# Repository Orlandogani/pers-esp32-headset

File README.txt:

This project is for custom headset Electronics PCB Routing. The name is coming from the acronym of my own name.

ORGA: Omni Radiant Gaming Apparatus
Vibe & Product Fit: Flagship RGB peripherals—think high-end wireless mice and master-class headsets designed for professional esports athletes who demand absolute dominance.

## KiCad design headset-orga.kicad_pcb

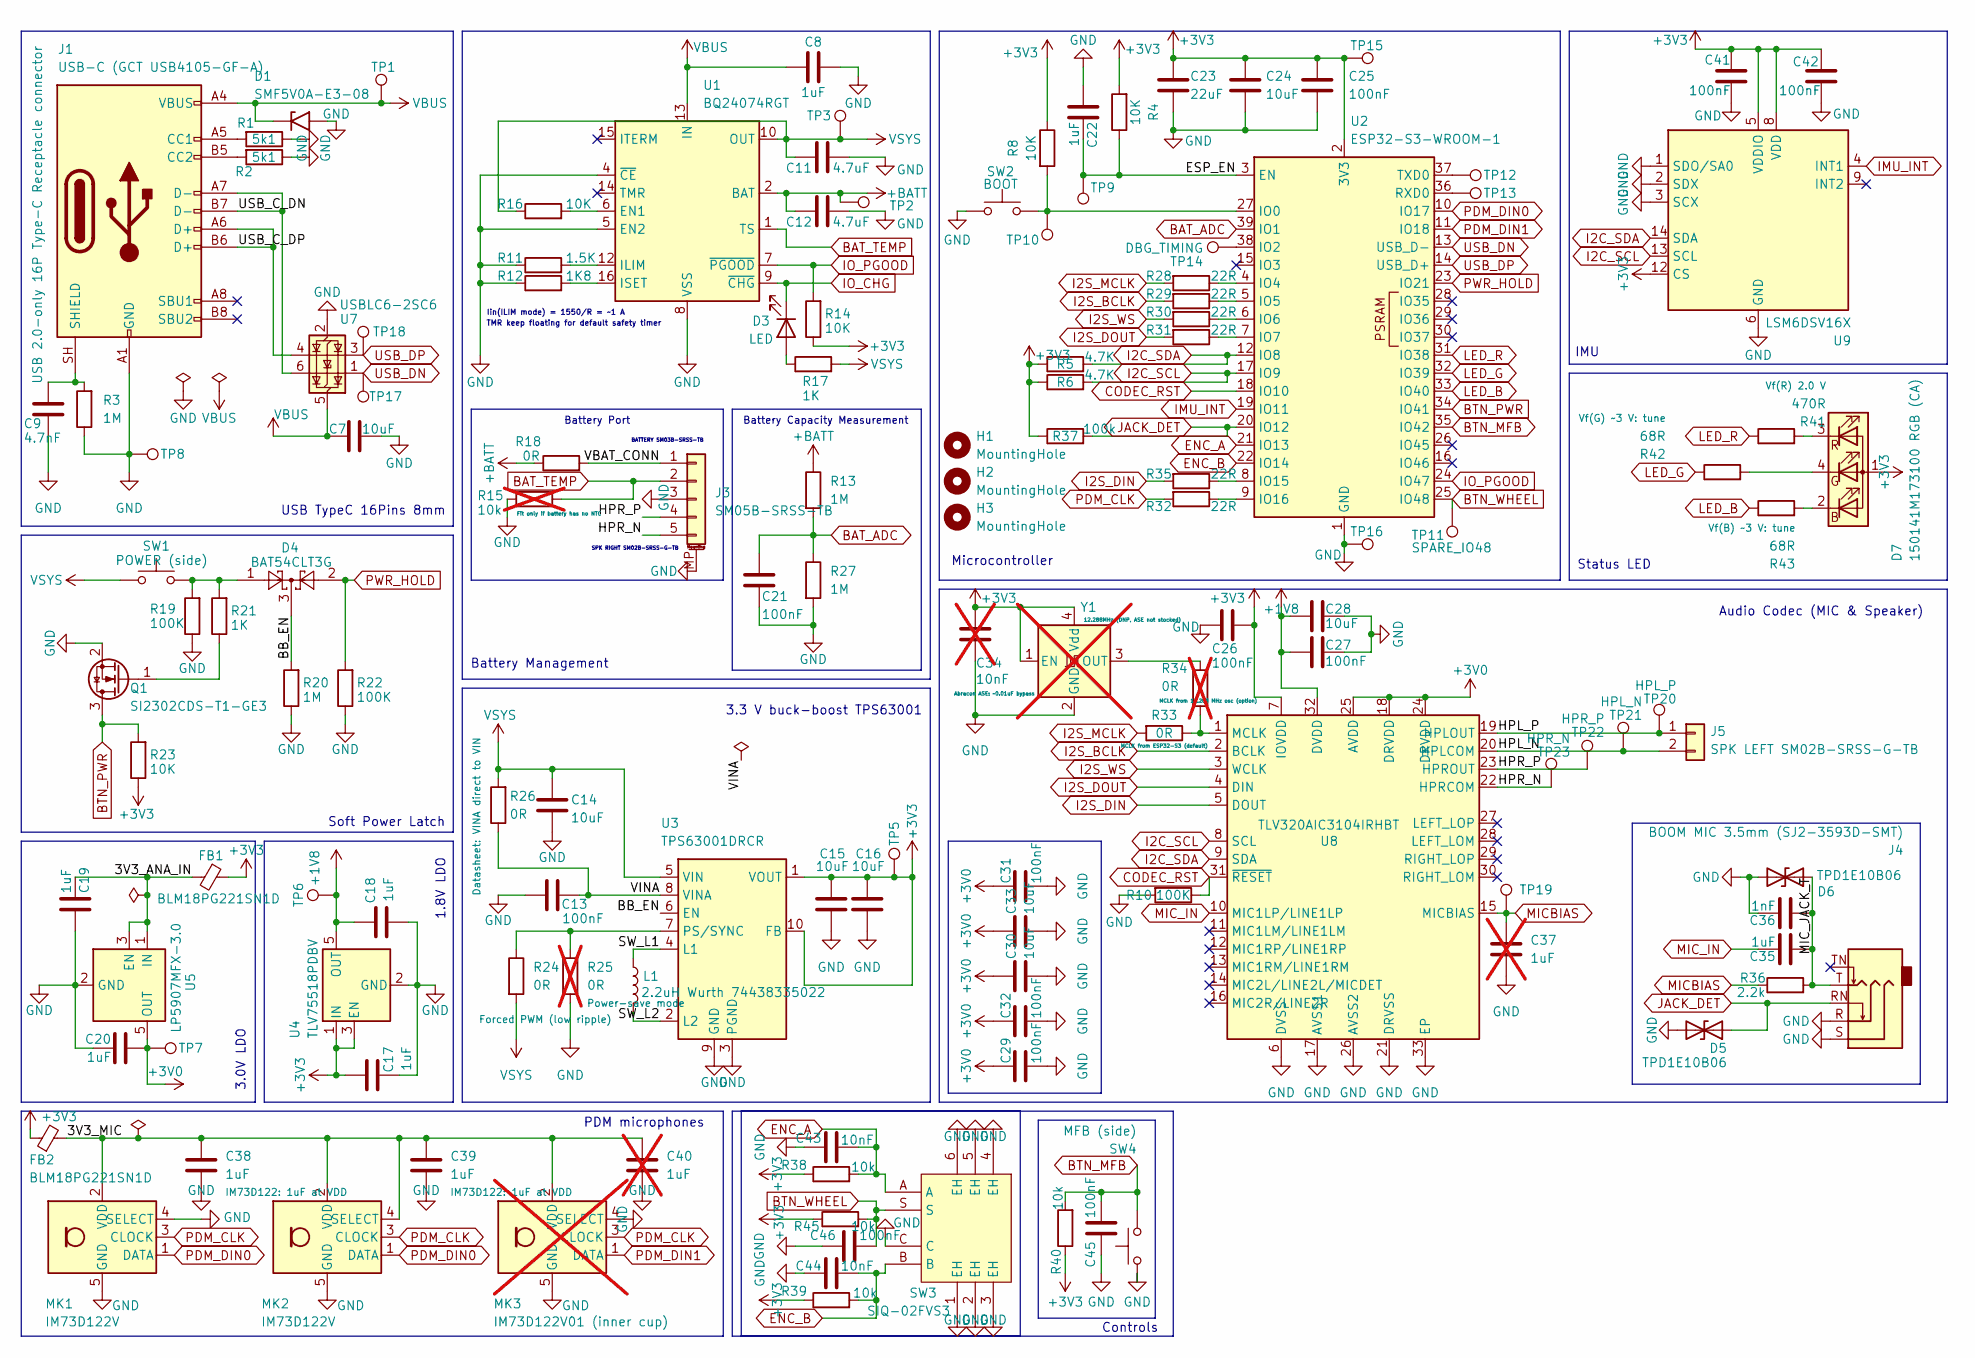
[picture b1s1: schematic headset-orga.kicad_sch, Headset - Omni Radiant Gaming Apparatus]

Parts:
C7: 10uF; C_0805_2012Metric
C8, C17, C18, C19, C20: 1uF; C_0603_1608Metric
C9: 4.7nF; C_0402_1005Metric
C11, C12: 4.7uF; C_0603_1608Metric
C13, C21, C25, C26, C27, C29, C31, C32, C41, C42, C45, C46: 100nF; C_0402_1005Metric
C14, C15, C16, C24: 10uF; C_0603_1608Metric
C22, C35, C38, C39: 1uF; C_0402_1005Metric
C23: 22uF; C_0805_2012Metric
C28, C30, C33: 10uF; C_0402_1005Metric
C34: 10nF; C_0402_1005Metric; not fitted
C36: 1nF; C_0402_1005Metric
C37, C40: 1uF; C_0402_1005Metric; not fitted
C43, C44: 10nF; C_0402_1005Metric
D1: SMF5V0A-E3-08; D_SMF
D3: LED; LED_0603_1608Metric
D4: BAT54CLT3G; SOT-23
D5, D6: TPD1E10B06; D_0402_1005Metric
D7: 150141M173100 RGB (CA); LED_RGB_Wuerth-PLCC4_3.2x2.8mm_150141M173100
FB1, FB2: BLM18PG221SN1D; L_0603_1608Metric
H1, H2, H3: MountingHole; MountingHole_2.4mm_M2
J1: USB-C (GCT USB4105-GF-A); USB_C_Receptacle_GCT_USB4105-xx-A_16P_TopMnt_Horizontal
J3: SM05B-SRSS-TB; JST_SH_SM05B-SRSS-TB_1x05-1MP_P1.00mm_Horizontal
J4: BOOM MIC 3.5mm (SJ2-3593D-SMT); Jack_3.5mm_CUI_SJ2-3593D-SMT_Horizontal
J5: SPK LEFT SM02B-SRSS-G-TB; JST_SH_SM02B-SRSS-TB_1x02-1MP_P1.00mm_Horizontal
L1: 2.2uH Wurth 74438335022; L_Wuerth_MAPI-3015
MK1, MK2: IM73D122V; Infineon_PG-LLGA-5-3_IM73D122
MK3: IM73D122V01 (inner cup); Infineon_PG-LLGA-5-3_IM73D122; not fitted
Q1: SI2302CDS-T1-GE3; SOT-23
R1, R2: 5k1; R_0603_1608Metric
R3, R20: 1M; R_0603_1608Metric
R4, R8, R14, R16, R23: 10K; R_0603_1608Metric
R5, R6: 4.7K; R_0603_1608Metric
R10, R19, R22: 100K; R_0603_1608Metric
R11: 1.5K; R_0603_1608Metric
R12: 1K8; R_0603_1608Metric
R13, R27: 1M; R_0402_1005Metric
R15: 10k; R_0402_1005Metric; not fitted
R17, R21: 1K; R_0603_1608Metric
R18, R33: 0R; R_0603_1608Metric
R24, R26: 0R; R_0402_1005Metric
R25, R34: 0R; R_0402_1005Metric; not fitted
R28, R29, R30, R31, R32, R35: 22R; R_0603_1608Metric
R36: 2.2k; R_0603_1608Metric
R37: 100k; R_0603_1608Metric
R38, R39, R40, R45: 10k; R_0402_1005Metric
R41: 470R; R_0402_1005Metric
R42, R43: 68R; R_0402_1005Metric
SW1: POWER (side); SW_SPST_EVQP7A
SW2: BOOT; SW_SPST_EVQP7A
SW3: SIQ-02FVS3; SW-SMD_SIQ-02FVS3_1; MPN SIQ-02FVS3; LCSC C2925423
SW4: MFB (side); SW_SPST_EVQP7A
TP1, TP2, TP3, TP5, TP6, TP7, TP8, TP9, TP10, TP15, TP16, TP17, TP18, TP19: TestPoint; TestPoint_Pad_D1.0mm
TP11: SPARE_IO48; TestPoint_Pad_D1.0mm
TP12: TX0; TestPoint_Pad_D1.0mm
TP13: RX0; TestPoint_Pad_D1.0mm
TP14: DBG_TIMING; TestPoint_Pad_D1.0mm
TP20: HPL_P; TestPoint_Pad_D1.0mm
TP21: HPL_N; TestPoint_Pad_D1.0mm
TP22: HPR_P; TestPoint_Pad_D1.0mm
TP23: HPR_N; TestPoint_Pad_D1.0mm
U1: BQ24074RGT; VQFN-16-1EP_3x3mm_P0.5mm_EP1.6x1.6mm_ThermalVias
U2: ESP32-S3-WROOM-1
U3: TPS63001DRCR; Texas_DRC0010J_ThermalVias
U4: TLV75518PDBV; SOT-23-5
U5: LP5907MFX-3.0; SOT-23-5
U7: USBLC6-2SC6; SOT-23-6
U8: TLV320AIC3104IRHBT; Texas_RHB0032E_VQFN-32-1EP_5x5mm_P0.5mm_EP3.45x3.45mm_Therm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
U9: LSM6DSV16X; LGA-14_3x2.5mm_P0.5mm_LayoutBorder3x4y
Y1: 12.288MHz (DNP, ASE not stocked); Oscillator_SMD_Abracon_ASE-4Pin_3.2x2.5mm; not fitted

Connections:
+1V8: C18.2, C27.1, C28.1, TP6.1 (1_1), U4.5 (OUT), U8.32 (DVDD)
+3V0: C20.2, C29.1, C30.1, C31.1, C32.1, C33.1, TP7.1 (1_1), U5.5 (OUT), U8.18 (DRVDD), U8.24 (DRVDD), U8.25 (AVDD)
+3V3: C15.2, C16.2, C17.2, C23.1, C24.1, C25.1, C26.2, C34.1, C41.1, C42.1, D7.1 (A), FB1.1, FB2.1, R4.2, R5.1, R6.1, R8.1, R14.1, R23.1, R37.1, R38.1, R39.1, R40.1, R45.1, TP5.1 (1_1), TP15.1 (1_1), U2.2 (3V3), U3.1 (VOUT), U3.10 (FB), U4.1 (IN), U4.3 (EN), U8.7 (IOVDD), U9.5 (VDDIO), U9.8 (VDD), U9.12 (CS), Y1.1 (EN), Y1.4 (Vdd)
+BATT: C12.1, R13.1, R18.1, TP2.1 (1_1), U1.2 (BAT), U1.3 (BAT)
/3V3_ANA_IN: C19.1, FB1.2, U5.1 (IN), U5.3 (EN)
/3V3_MIC: C38.1, C39.1, C40.1, FB2.2, MK1.2 (VDD), MK2.2 (VDD), MK2.4 (SELECT), MK3.2 (VDD)
/BB_EN: D4.3, R20.2, U3.6 (EN)
/ESP_EN: C22.2, R4.1, TP9.1 (1_1), U2.3 (EN)
/HPL_N: J5.2, TP21.1 (1_1), U8.20 (HPLCOM)
/HPL_P: J5.1, TP20.1 (1_1), U8.19 (HPLOUT)
/HPR_N: J3.5, TP23.1 (1_1), U8.22 (HPRCOM)
/HPR_P: J3.4, TP22.1 (1_1), U8.23 (HPROUT)
/MIC_JACK_T: C35.2, C36.2, D6.1 (A1), J4.T, R36.2
/SW_L1: L1.1, U3.4 (L1)
/SW_L2: L1.2, U3.2 (L2)
/USB_C_DN: J1.A7 (D-), J1.B7 (D-), U7.6 (I/O1)
/USB_C_DP: J1.A6 (D+), J1.B6 (D+), U7.4 (I/O2)
/VBAT_CONN: J3.1, R18.2
/VINA: C13.2, R26.1, U3.8 (VINA)
BAT_ADC: C21.1, R13.2, R27.1, U2.39 (IO1)
BAT_TEMP: J3.2, R15.1, U1.1 (TS)
BTN_MFB: C45.2, R40.2, SW4.2, U2.35 (IO42)
BTN_PWR: Q1.3 (D), R23.2, U2.34 (IO41)
BTN_WHEEL: C46.2, R45.2, SW3.S, TP11.1 (1_1), U2.25 (IO48)
CODEC_RST: R10.1, U2.18 (IO10), U8.31 (~RESET)
ENC_A: C43.2, R38.2, SW3.A, U2.21 (IO13)
ENC_B: C44.2, R39.2, SW3.B, U2.22 (IO14)
GND: C7.2, C8.2, C9.2, C11.2, C12.2, C13.1, C14.1, C15.1, C16.1, C17.1, C18.1, C19.2, C20.1, C21.2, C22.1, C23.2, C24.2, C25.2, C26.1, C27.2, C28.2, C29.2, C30.2, C31.2, C32.2, C33.2, C34.2, C36.1, C37.2, C38.2, C39.2, C40.2, C41.2, C42.2, C43.1, C44.1, C45.1, C46.1, D1.2 (A2), D5.2 (A2), D6.2 (A2), J1.A1 (GND), J1.A12 (GND), J1.B1 (GND), J1.B12 (GND), J3.3, J3.MP (MountPin), J4.R, J4.S, MK1.4 (SELECT), MK1.5 (GND), MK2.5 (GND), MK3.4 (SELECT), MK3.5 (GND), Q1.2 (S), R1.1, R2.1, R3.1, R10.2, R11.1, R12.1, R15.2, R19.1, R20.1, R22.1, R25.2, R27.2, SW2.1, SW3.1 (EH), SW3.2 (EH), SW3.3 (EH), SW3.4 (EH), SW3.5 (EH), SW3.6 (EH), SW3.C, SW4.1, TP8.1 (1_1), TP16.1 (1_1), U1.4 (~CE), U1.5 (EN2), U1.8 (VSS), U1.17 (VSS), U2.1 (GND), U2.40 (GND), U2.41 (GND), U3.3 (PGND), U3.9 (GND), U3.11 (PGND), U4.2 (GND), U5.2 (GND), U7.2 (GND), U8.6 (DVSS), U8.17 (AVSS1), U8.21 (DRVSS), U8.26 (AVSS2), U8.33 (EP), U9.1 (SDO/SA0), U9.2 (SDX), U9.3 (SCX), U9.6 (GND), U9.7 (GND), Y1.2 (GND)
I2C_SCL: R6.2, U2.17 (IO9), U8.8 (SCL), U9.13 (SCL)
I2C_SDA: R5.2, U2.12 (IO8), U8.9 (SDA), U9.14 (SDA)
I2S_BCLK: R29.2, U8.2 (BCLK)
I2S_DIN: R35.2, U8.5 (DOUT)
I2S_DOUT: R31.2, U8.4 (DIN)
I2S_MCLK: R28.2, R33.2
I2S_WS: R30.2, U8.3 (WCLK)
IMU_INT: U2.19 (IO11), U9.4 (INT1)
IO_CHG: D3.1 (K), U1.9 (~CHG)
IO_PGOOD: R14.2, U1.7 (~PGOOD), U2.24 (IO47)
JACK_DET: D5.1 (A1), J4.RN, R37.2, U2.20 (IO12)
LED_B: R43.1, U2.33 (IO40)
LED_G: R42.1, U2.32 (IO39)
LED_R: R41.1, U2.31 (IO38)
MICBIAS: C37.1, R36.1, TP19.1 (1_1), U8.15 (MICBIAS)
MIC_IN: C35.1, U8.10 (MIC1LP/LINE1LP)
unnamed: D3.2 (A), R17.1
unnamed: D4.1, R19.2, R21.2, SW1.2
unnamed: D7.2 (BK), R43.2
unnamed: D7.4 (GK), R42.2
unnamed: D7.3 (RK), R41.2
unnamed: J1.A5 (CC1), R1.2
unnamed: J1.B5 (CC2), R2.2
unnamed: C9.1, J1.SH (SHIELD), R3.2
unnamed: Q1.1 (G), R21.1
unnamed: R16.2, U1.6 (EN1)
unnamed: R11.2, U1.12 (ILIM)
unnamed: R12.2, U1.16 (ISET)
unnamed: R8.2, SW2.2, TP10.1 (1_1), U2.27 (IO0)
unnamed: TP14.1 (1_1), U2.38 (IO2)
unnamed: R28.1, U2.4 (IO4)
unnamed: R29.1, U2.5 (IO5)
unnamed: R30.1, U2.6 (IO6)
unnamed: R31.1, U2.7 (IO7)
unnamed: R35.1, U2.8 (IO15)
unnamed: R32.1, U2.9 (IO16)
unnamed: TP13.1 (1_1), U2.36 (RXD0)
unnamed: TP12.1 (1_1), U2.37 (TXD0)
unnamed: R24.1, R25.1, U3.7 (PS/SYNC)
unnamed: R33.1, R34.2, U8.1 (MCLK)
unnamed: R34.1, Y1.3 (OUT)
PDM_CLK: MK1.3 (CLOCK), MK2.3 (CLOCK), MK3.3 (CLOCK), R32.2
PDM_DIN0: MK1.1 (DATA), MK2.1 (DATA), U2.10 (IO17)
PDM_DIN1: MK3.1 (DATA), U2.11 (IO18)
PWR_HOLD: D4.2, R22.2, U2.23 (IO21)
USB_DN: TP17.1 (1_1), U2.13 (USB_D-), U7.1 (I/O1)
USB_DP: TP18.1 (1_1), U2.14 (USB_D+), U7.3 (I/O2)
VBUS: C7.1, C8.1, D1.1 (A1), J1.A4 (VBUS), J1.A9 (VBUS), J1.B4 (VBUS), J1.B9 (VBUS), TP1.1 (1_1), U1.13 (IN), U7.5 (VBUS)
VSYS: C11.1, C14.2, R16.1, R17.2, R24.2, R26.2, SW1.1, TP3.1 (1_1), U1.10 (OUT), U1.11 (OUT), U3.5 (VIN)

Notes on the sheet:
1.8V LDO
3.0V LDO
Battery Capacity Measurement
3.3 V buck-boost TPS63001
Soft Power Latch
Controls
BATTERY SM03B-SRSS-TB
Iin(ILIM mode) = 1550/R = ~1 A
Battery Port
IMU
Microcontroller
Audio Codec (MIC & Speaker)
PDM microphones
TMR keep floating for default safety timer
Status LED
Battery Management
USB TypeC 16Pins 8mm
SPK RIGHT SM02B-SRSS-G-TB

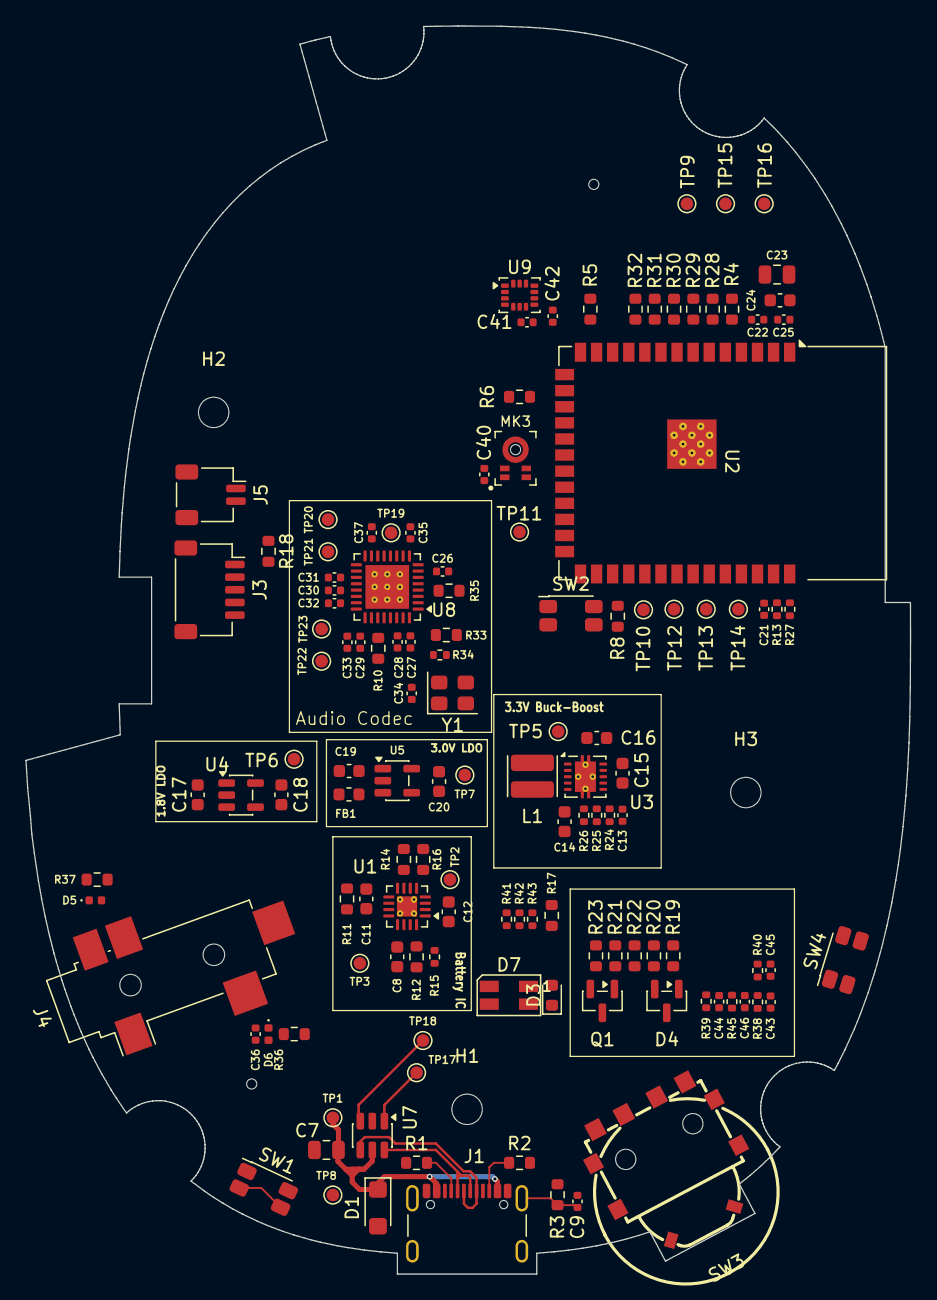
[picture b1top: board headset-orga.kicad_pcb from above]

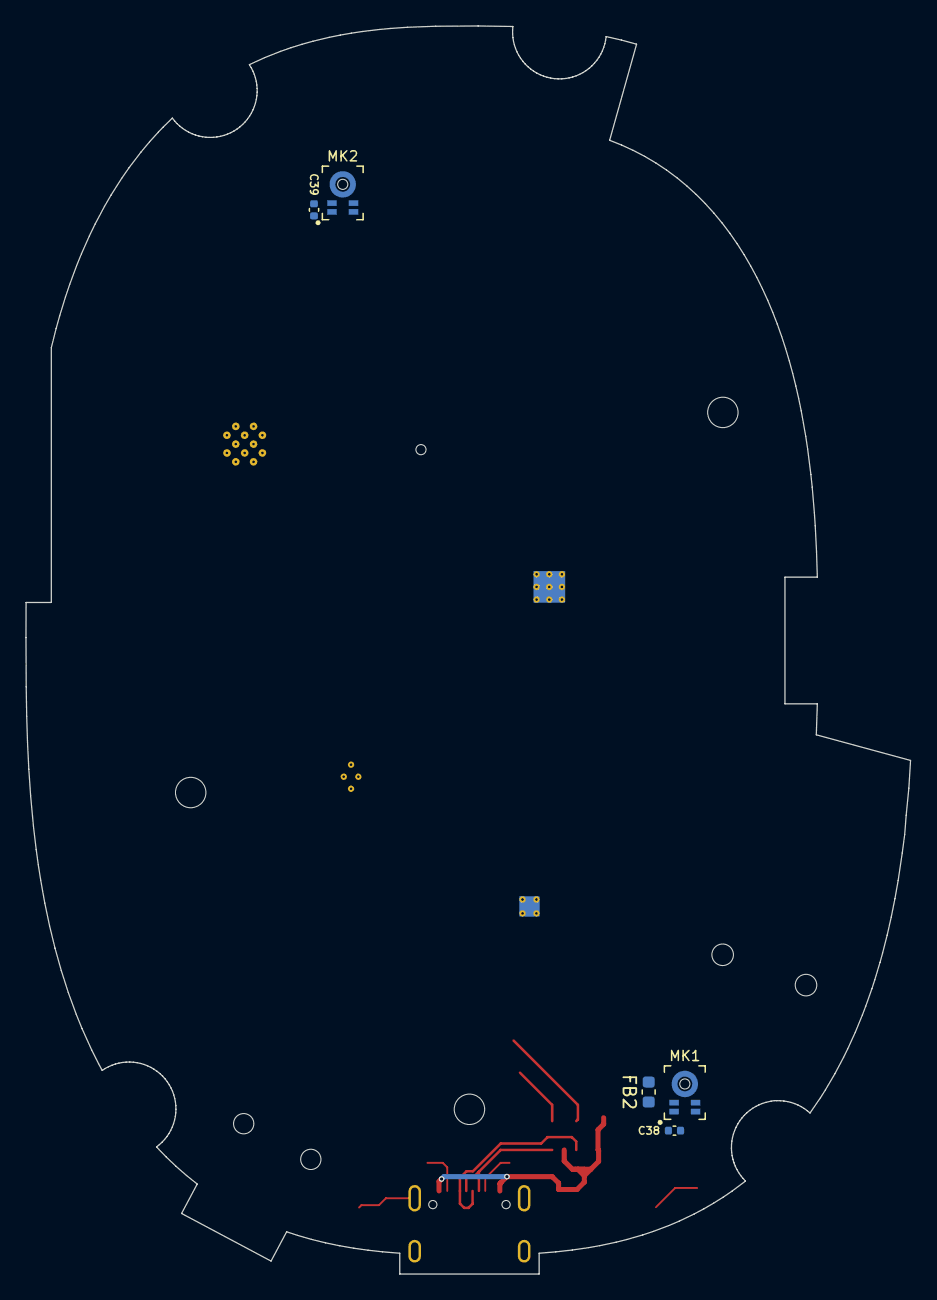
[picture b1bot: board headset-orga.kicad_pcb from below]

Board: 4 copper layers, 69.8 x 98.5 mm, 136 parts (5 on the bottom side), 77 nets.
